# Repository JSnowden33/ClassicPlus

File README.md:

# Classic+
Classic+ is a hardware emulator that replaces the Wii Classic Controller and Nunchuk.  

### Usage
Classic+ normally operates as a Classic Controller. Nunchuk mode can be enabled at any time by connecting the MD pin to GND. The device can be temporarily disabled by connecting the EN pin to GND. The SDA, SCL, and DET pins should be connected to a Wii Remote expansion port. Unofficial Wii Remotes may not be supported.

The Wii Remote IR camera can be emulated using the right joystick only in Nunchuk mode. This feature is only supported on non-TR Wii Remotes. The real IR camera must be removed from the Wii Remote before using IR camera emulation. Sensitivity adjustment is available in the homebrew app.

Soldering the accelerometer IC is optional. Without it, Nunchuk mode will report neutral values.

Classic+ works with Wii Remotes and SNES Classic. NES Classic support is untested.

PCBs can be ordered here: https://oshpark.com/shared_projects/poSQyyw2
  
### Updating
Place `update.hex` from the Firmware folder on the root of an SD card or USB storage device. Run the Wii homebrew app with a Classic+ board connected to a Wii Remote and select "Update Classic+". Note that the update process can take up to 10 minutes.

### Safe Mode
Safe mode can be enabled by holding the X and Y buttons when the Classic+ powers on. Safe mode only supports updating through the homebrew app. Buttons, joysticks, and calibration will not work.
  
### Programming
Flash the pre-compiled `firmware.hex` using MPLAB IPE with a PICkit 3.

### Compiling
Make a project in MPLAB X IDE for PIC16F18876 with the XC8 compiler. The Bootloader and Main Program must be compiled as separate projects and flashed onto the same device using the code offset and Preserve Program Memory features or by manually combining the compiled .hex files.

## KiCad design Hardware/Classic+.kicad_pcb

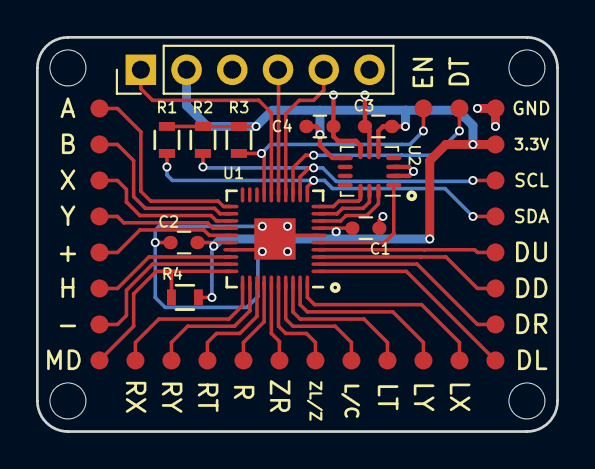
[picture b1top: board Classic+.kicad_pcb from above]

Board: 2 copper layers, 28.9 x 21.9 mm, 39 parts (0 on the bottom side), 35 nets.

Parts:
C1, C2, C3, C5: C; C_0603
J1, J2, J3, J4, J5, J6, J8, J9, J10, J11, J12, J13, J14, J15, J16, J17, J18, J19, J20, J21, J22, J23, J24, J25, J26, J27, J29, J32: TEST_1P; Test_Pad
J7: CONN_01X06; Pin_Header_Straight_1x06_Pitch2.54mm
R1, R2, R3, R4: R; R_0603
U1: PIC16F18875; QFN-40-1EP_5x5mm_Pitch0.4mm
U2: LSM6DS; LGA-14_3x2.5mm_Pitch0.5mm

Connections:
/+: J15.1, U1.25
/-: J19.1, U1.29
/A: J1.1, U1.21
/B: J4.1, U1.22
/CS: U1.10, U2.12
/DD: J18.1, U1.3
/DET: J29.1, U1.13
/DL: J24.1, U1.1
/DR: J21.1, U1.2
/DU: J14.1, U1.4
/EN: J32.1, R4.2, U1.17
/H: J22.1, U1.28
/ICSPCLK: J7.5, U1.14
/ICSPDAT: J7.4, U1.15
/L: J2.1, U1.37
/LT: J16.1, U1.38
/LX: J3.1, U1.40
/LY: J6.1, U1.39
/MCLR: J7.1, U1.16
/MISO: U1.5, U2.1
/MODE: J27.1, R3.2, U1.30
/MOSI: U1.8, U2.14
/R: J9.1, U1.34
/RT: J20.1, U1.33
/RX: J10.1, U1.31
/RY: J13.1, U1.32
/SCK: U1.9, U2.13
/SCL: J26.1, R2.2, U1.12
/SDA: J25.1, R1.2, U1.11
/X: J8.1, U1.23
/Y: J11.1, U1.24
/ZL: J5.1, U1.36
/ZR: J12.1, U1.35
GND: C1.2, C2.1, C3.1, C5.1, J7.3, J23.1, U1.6, U1.27, U1.41, U2.2, U2.3, U2.6, U2.7
VDD: C1.1, C2.2, C3.2, C5.2, J7.2, J17.1, R1.1, R2.1, R3.1, R4.1, U1.7, U1.26, U2.5, U2.8

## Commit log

2018-07-16 Add IR camera compatibility
2018-07-16 Update register addresses
2018-07-16 Add axis readings for Nunchuk mode
2018-07-16 Add EEPROM addresses
2019-05-20 Attach image
